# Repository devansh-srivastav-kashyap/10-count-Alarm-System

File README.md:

# 10-count-Alarm-System

This PCB has been constructed in such a way that i counts to 10 and as soon as 10 counts is reached, the device resets itself and play a buzzer. It is designed for the given problem statement by an industry to count the number of products and alarm the user of te completion of the badge. 

Counting is done using Push Button.

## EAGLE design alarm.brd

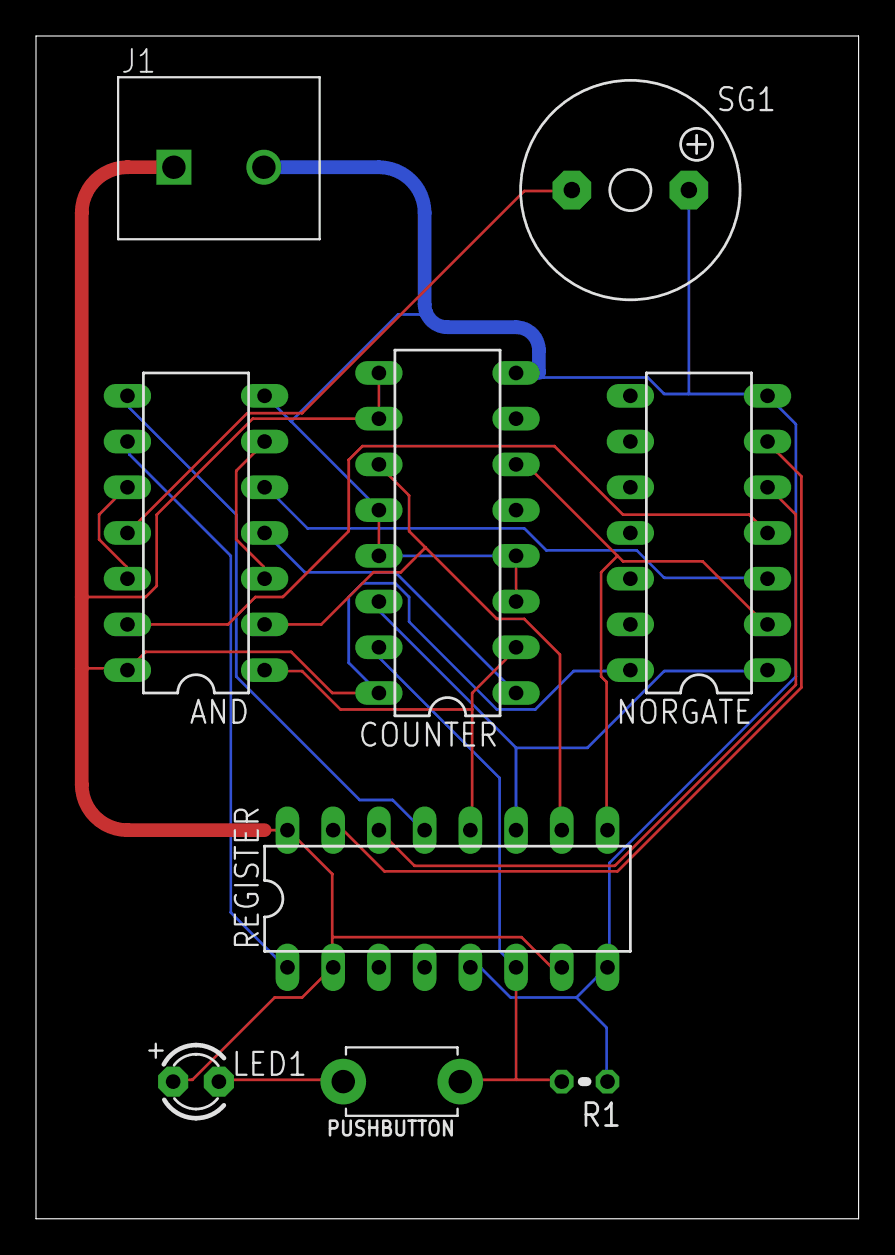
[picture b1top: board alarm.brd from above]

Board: 2 copper layers, 45.7 x 65.7 mm, 9 parts (0 on the bottom side), 18 nets.

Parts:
AND: 4081N; DIL14
COUNTER: 4029N; DIL16
J1: OSTTA020161; OST_OSTTA020161
LED1: RED; LED3MM
NORGATE: 4001N; DIL14
PUSHBUTTON: TACT_PANA-EVQ
R1: 200; 0204V
REGISTER: 4035N; DIL16
SG1: F/QMX

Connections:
+5V: AND.14, COUNTER.9, COUNTER.10, COUNTER.16, J1.1, LED1.A, NORGATE.14, REGISTER.2, REGISTER.7, REGISTER.16
CLOCK: COUNTER.15, PUSHBUTTON.P$1, R1.2, REGISTER.6
GND: AND.7, COUNTER.3, COUNTER.4, COUNTER.8, COUNTER.12, COUNTER.13, J1.2, NORGATE.7, R1.1, REGISTER.5, REGISTER.8, SG1.+
unnamed: LED1.K, PUSHBUTTON.P$2
unnamed: AND.3, AND.6
unnamed: AND.1, COUNTER.2, REGISTER.12
unnamed: COUNTER.14, NORGATE.1, REGISTER.11
unnamed: AND.2, COUNTER.11, REGISTER.10
unnamed: COUNTER.6, NORGATE.2, REGISTER.9
unnamed: AND.5, NORGATE.3
unnamed: AND.8, REGISTER.13
unnamed: AND.9, REGISTER.1
unnamed: NORGATE.6, REGISTER.15
unnamed: NORGATE.5, REGISTER.14
unnamed: AND.10, AND.12
unnamed: AND.13, NORGATE.4
unnamed: AND.11, SG1.-
RES: AND.4, COUNTER.1

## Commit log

2021-03-27 Gerber File
2021-03-27 Schematic
2021-03-27 Board Layout
2021-03-27 Prototype
2022-02-21 Schematic Diagram
